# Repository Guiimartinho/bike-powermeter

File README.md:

<div align="center">

# Bike Power Meter

**Medidor de potência para bicicleta, aberto do extensômetro ao pod: torque por ponte de classe transdutor colada no braço do pedivela, cadência por acelerômetro, potência por BLE e ANT+. Par do [GNSS Bike Computer](https://github.com/Guiimartinho/gnss-bike-computer).**

</div>

Um módulo colado na face interna do braço esquerdo do pedivela. A ponte de extensômetros mede a **deformação do próprio braço**, que é o elemento elástico; o conversor lê a ponte em 24 bits, o acelerômetro dá o ângulo e a cadência, e o rádio publica potência, cadência e equilíbrio como qualquer medidor comercial — em **BLE Cycling Power** e **ANT+ Bicycle Power**, para o ciclocomputador do projeto ou para qualquer aplicativo.

O firmware é **obra original** em C puro sobre Zephyr, não um port. A placa, o pod e todos os desenhos são **gerados por programa** a partir dos documentos de [`hardware_powermeter/`](hardware_powermeter/README.md), pela mesma ideia do ciclocomputador: um gerador, um dry run, e nenhum número que não venha de uma ficha ou de uma medida.

> [!WARNING]
> **Nada foi fabricado, impresso, soldado nem colado, e o firmware nunca rodou.** Não existe placa física, nenhum extensômetro foi colado num pedivela, nenhum componente passou por bancada e nenhuma linha de código foi vista funcionando: tudo o que está escrito abaixo foi verificado no PC. As medidas do braço do pedivela são **lugares reservados** — ninguém mediu o braço. O estado de cada área está em [docs/07-status.md](docs/07-status.md).

## Índice

- [Visão geral](#visão-geral)
- [O aparelho](#o-aparelho)
- [Como a potência sai da deformação](#como-a-potência-sai-da-deformação)
- [Componentes](#componentes)
- [Funcionalidades](#funcionalidades)
- [Início rápido](#início-rápido)
- [Estrutura](#estrutura)
- [Documentação](#documentação)
- [Estado e próximos passos](#estado-e-próximos-passos)
- [Créditos e licença](#créditos-e-licença)

## Visão geral

```mermaid
flowchart LR
    subgraph POD["Pod colado no braço esquerdo"]
        G["Ponte S5229<br/>5 kΩ, uma peça"] -->|"2 mV"| A["ADS1220<br/>24 bits, ganho 128"]
        I["BMA400<br/>ângulo e cadência"] --> M["nRF54L15<br/>HOLYIOT-26001-A"]
        T["TMP117<br/>±0,1 °C"] --> M
        A --> M
        P["nPM1100 + célula LiPo"] --> M
        C["conector magnético<br/>carga, serial, SWD"] --> P
    end
    M -- "BLE Cycling Power" --> CC["ciclocomputador<br/>ou qualquer app"]
    M -- "ANT+ Bicycle Power" --> CC
```

## O aparelho

<div align="center">

*O pod no braço do pedivela. O braço é um lugar reservado, desenhado da classe (170 mm entre eixos) até o do dono ser medido; o pod, a placa e a ponte são a geometria real do projeto.*

</div>

### O produto, peça por peça

| | |
|---|---|
|  |  |
| *A pilha inteira: tampa, anel O, placa, célula e concha* | *De lado: 7,7 mm do fundo ao topo da tampa* |
|  |  |
| *Aberto: a ponte fica no **braço**, não no pod, e cinco fios sobem por um rasgo no fundo* | *A ponte S5229 colada na face interna do braço* |

### O pod

| | |
|---|---|
|  |  |
| *Fechado: 73,5 × 20,0 × 7,7 mm, 14,3 g estimados* | *Explodido: concha, célula, placa, anel O e tampa* |
|  |  |
| *Aberto, com a placa assentada* | *A célula no berço, no passo em que ela entra* |
|  |  |
| *A tampa por dentro: sulco do anel O, dedos da placa e o ressalto que comprime a junta da porta* | *Por baixo: a base de colagem de 14 mm, o relevo de 0,5, o rasgo dos fios, o bolso do extensômetro e a canaleta do feixe* |

### A placa

| | |
|---|---|
|  |  |
| *A placa, 50 × 16 mm em 4 camadas, 58 peças* | *O verso: pads de teste e o que não precisa ser alcançado, sobre o fundo rebaixado do pod* |
|  |  |
| *Em ângulo, com o corpo real de cada peça* | *O mapa de montagem, peça a peça* |

O envelope de referência veio de **fotogrametria** sobre as fotos de imprensa de um medidor da classe, porque nenhum fabricante publica as medidas: 37 a 39 mm de comprimento, 18 a 22 de largura e 9 a 13 de altura, com a escala aferida por dois caminhos independentes ([docs/01](docs/01-visao-geral.md)). É contra esse número que o pod é medido.

## Como a potência sai da deformação

O que quase todo texto sobre medidores esconde: **o sensor não mede força, mede o quanto o braço entorta.**

```mermaid
flowchart LR
    F["força no pedal<br/>~500 N"] --> D["o braço flexiona<br/>~571 µε na borda"]
    D --> V["a ponte desequilibra<br/>~2,28 mV"]
    V --> N["ADS1220, ganho 128<br/>24 bits ratiométrico"]
    N --> TQ["torque<br/>zero, inclinação, temperatura"]
    TQ --> PW["potência = torque × ω"]
    ANG["BMA400<br/>ângulo e ω"] --> PW
```

Duas coisas foram **medidas e corrigidas** aqui, e as duas mudam o aparelho:

- **o padrão de extensômetro especificado estava errado.** A lista pedia padrão de cisalhamento a 45°, que é padrão de torquímetro de eixo; o braço do pedivela é uma viga em balanço. Na mesma seção, a grade a 45° lê 52 µε e a grade axial na borda lê 459 µε: **8,9 vezes mais** ([docs/06](docs/06-medicao-e-calibracao.md));
- **o braço Shimano é oco.** Com parede de 3 mm o momento de inércia cai de 9.333 para 7.504 mm⁴ e a deformação sobe de 459 para **571 µε**, 24 % a mais.

A ponte é **uma peça só**, não quatro colagens: o padrão S5229 do databook de classe transdutor, `N2K-13-S5229A-50C/DG/E3`, 5 kΩ ±5 %, matriz de 4,0 × 3,7 mm, ponte de Poisson já balanceada de fábrica. O código `13` é a autocompensação para alumínio; **sem ele escrito no pedido o fabricante embarca o `06`, que é o de aço**.

## Componentes

| Bloco | Peça | Por quê |
|---|---|---|
| Ponte | Micro-Measurements `N2K-13-S5229A-50C/DG/E3` | ponte completa numa colagem só, 5 kΩ (0,6 mA em vez de 3,0), balanceada de fábrica, autocompensada para alumínio |
| Conversor | TI ADS1220 | 0,26 µV RMS com ganho 128, 585 µA medindo, referência **ratiométrica** (a excitação é a referência, então a tensão da célula sai da conta) |
| Cadência e ângulo | Bosch BMA400 | 850 nA a 25 Hz; driver próprio, porque o `bosch,bma4xx` da árvore usa o mapa do BMA422 |
| Temperatura | TI TMP117 | ±0,1 °C para o ajuste do zero e da inclinação |
| MCU e rádio | **HOLYIOT-26001-A** (nRF54L15), antena cerâmica | 10,0 × 12,5 mm contra 16,5 × 12,0 do ME54BS13: o módulo era **26 % da área da placa**, mais que as 37 peças pequenas somadas, e é a única alavanca de tamanho que move alguma coisa. Custa o USB, que este SoC não tem ([09](hardware_powermeter/09-modulo-de-radio.md)) |
| Carga e 3,0 V | Nordic nPM1100 | carregador e buck numa peça, 800 nA |
| Excitação | TI TPS22916 | desliga a ponte entre amostras; é ela que faz os 5 kΩ valerem a pena |
| Bateria | LiPo de bolsa classe **`401123`** (4,0 × 11 × 23 mm, ≥ 78 mAh, dois fios, proteção integrada) | a 0,68 mA — ponte de 5 kΩ com o conversor em duty-cycle — são **114 h**, contra as 50 h do requisito. A premissa anterior, de 2,5 mm de espessura, não existe: naquele volume a célula vale ~49 mAh. Nenhuma loja foi alcançada: o envelope é **requisito de compra** |
| Conector | magnético de 6 contatos, **desenhado aqui** | carga, serial e SWD num cabo só, sem tampa de borracha para perder. Contatos chatos de ouro no aparelho e molas no cabo, para o pod poder ser vedado ([06](hardware_powermeter/06-conectores-e-pontos-de-teste.md#j101--conector-magnético)) |

Lista completa, com a ficha e o código de compra de cada peça: [`hardware_powermeter/01-lista-de-componentes.md`](hardware_powermeter/01-lista-de-componentes.md).

## Funcionalidades

| Funcionalidade | Estado |
|---|---|
| Torque por ponte, com zero, inclinação e ajuste de temperatura | modelo escrito e testado no PC (18 casos, 50 de 50 linhas) |
| Ângulo e cadência pelos cruzamentos de zero do eixo tangencial | modelo escrito e testado (18 casos, 113 de 113 linhas) |
| Potência, equilíbrio e eficiência por volta | modelo escrito e testado (12 casos, 80 de 80 linhas) |
| Calibração: zero, inclinação por mínimos quadrados, massa conhecida | modelo escrito e testado (18 casos, 135 de 135 linhas) |
| BLE Cycling Power (Measurement, Feature, Control Point, Vector) | compila; os bytes vêm do modelo testado; nunca visto por um cliente |
| Serviço de configuração por BLE, com **escrita cifrada obrigatória** | compila; nunca emparelhado |
| ANT+ Bicycle Power (páginas 1, 16, 18, 80, 81) | compila com `ANT=1`; nenhum canal aberto de verdade |
| Atualização por BLE (mcumgr + MCUboot) e recuperação serial pela **UART** do conector magnético | compila; recusa pedalando ou com bateria fraca |
| Placa e pod gerados por programa, com dry run | placa colocada; pod fecha **16 de 16** regras, com vedação por anel O, parafusos, retenção e dreno |

## Início rápido

**Pré-requisitos** (Windows): nRF Connect SDK v3.3.0 em `C:\ncs` com o toolchain `936afb6332`, SEGGER J-Link e um nRF54LM20 DK. Para o ANT, o add-on `sdk-ant` em `C:\ncs\sdk-ant`, depois de aceitar o acordo ANT+. Para os testes de host, MinGW-w64 GCC, CMake e Ninja. Para o CAD, KiCad 8 em `D:\KiCAD`. Detalhes em [docs/03-ambiente-build.md](docs/03-ambiente-build.md).

```sh
# Git Bash, na raiz do repositório
bash tools/fw/fw.sh build            # compila para o nRF54LM20 DK (sysbuild + MCUboot)
BOARD=pmboard/nrf54l15/cpuapp BUILD_DIR=zephyr_app/build_custom bash tools/fw/fw.sh build
ANT=1 BUILD_DIR=zephyr_app/build_ant bash tools/fw/fw.sh build   # com a pilha ANT+
bash tools/fw/host_tests.sh          # 9 conjuntos, 134 casos
bash tools/fw/host_tests.sh coverage # e falha abaixo de 95 % em qualquer módulo
python tools/fw/board_check.py       # confere o devicetree contra o silício, docs/02 e o esquemático
python tools/docs/mermaid_check.py   # valida os diagramas da documentação
python tools/verificar_tudo.py       # a verificação inteira, três vezes
```

A cadeia de CAD, com o intérprete certo de cada etapa (o `fill_zones.py` **só** roda com o Python do KiCad), está em [`hardware_powermeter/cad/README.md`](hardware_powermeter/cad/README.md#a-cadeia).

O CI está **desligado**: a verificação é local.

## Estrutura

```mermaid
flowchart TB
    ROOT["bike_powermeter/"]
    ROOT --> ZA["zephyr_app/<br/>src (app · svc · model · rf) · include<br/>modules/pm_drivers (ADS1220, BMA400)<br/>boards · tests/host"]
    ROOT --> HW["hardware_powermeter/<br/>01 a 10 · cad (KiCad e geradores)<br/>esquematico · placa · pod (gerador, dry run, STL)<br/>datasheets (fora do git)"]
    ROOT --> DOCS["docs/<br/>01 a 07 · img/hardware (15 vistas)"]
    ROOT --> TOOLS["tools/<br/>fw · docs · verificar_tudo.py"]
    ROOT --> AI["CLAUDE.md · AGENTS.md · .claude/skills/"]
```

## Documentação

| Documento | Assunto |
|---|---|
| [01 · Visão geral](docs/01-visao-geral.md) | o que é, o envelope da classe por fotogrametria, as fases |
| [02 · Hardware](docs/02-hardware.md) | blocos da placa, pinos do módulo, orçamento de consumo, pod |
| [03 · Ambiente e build](docs/03-ambiente-build.md) | NCS v3.3.0, os três alvos, scripts, gravação |
| [04 · Arquitetura do firmware](docs/04-arquitetura-firmware.md) | os seis serviços, threads, pilhas, máquinas de estado |
| [05 · Protocolos](docs/05-protocolos.md) | BLE Cycling Power, ANT+ Bicycle Power, serviço de configuração com os UUID |
| [06 · Medição e calibração](docs/06-medicao-e-calibracao.md) | da deformação ao torque, flexão × cisalhamento, zero, inclinação, temperatura, saúde |
| [07 · Status](docs/07-status.md) | o que existe, o que foi verificado e como, o que falta |
| [Hardware](hardware_powermeter/README.md) | o esquemático, a placa, o pod, os dry runs e o que falta antes de fabricar |
| [CAD](hardware_powermeter/cad/README.md) | os geradores, as regras e as armadilhas medidas |
| [Pod](hardware_powermeter/pod/README.md) | o gerador do invólucro, as 32 regras do dry run e o que é decisão do desenho |
| [Módulo de rádio](hardware_powermeter/09-modulo-de-radio.md) | o HOLYIOT-26001-A: por que entrou, o que o nRF54L15 muda, pinagem, mecânica, a antena |
| [A classe medida](hardware_powermeter/12-comparacao-com-a-classe.md) | o 4iiii Precision 3+ e o U2e V4 contra o nosso, e o que custaria chegar ao alvo de envelope |
| [CHANGELOG](CHANGELOG.md) | histórico de mudanças |

## Estado e próximos passos

- **Feito em 2026-09-27:** a documentação de requisitos, arquitetura, protocolos e método de medição com as referências; a lista de componentes fechada por ficha; os nove módulos do modelo escritos e testados no PC (134 casos, 100 % das linhas, doze mutações mortas); o firmware embarcado inteiro compilando com **zero avisos** nos três alvos; o esquemático, a placa e o pod gerados por programa com os dois dry runs.
- **Feito em 2026-09-28:** a ponte fechada numa peça só (S5229 de 5 kΩ) com a designação de compra dos braços do dono; a correção do padrão de extensômetro (flexão, não cisalhamento: 8,9 vezes mais sinal); o roteador passou a ser julgado pelo **DRC do KiCad** em vez da própria contabilidade; três defeitos mecânicos do pod medidos e corrigidos, e o dry run fechou **12 de 12**.
- **Falta antes de fabricar:** fechar o roteamento, medir o pedivela do dono (quatro números), escolher a célula, fechar o conector magnético e conferir o empilhamento com o fabricante. A lista está em [`hardware_powermeter/README.md`](hardware_powermeter/README.md#antes-de-mandar-fabricar).
- **Depois:** bancada com massas de 5 a 20 kg contra o braço instrumentado, prova de estrada contra um medidor de referência até ±2 %, e a fase 2 no eixo de pedal.

## Créditos e licença

Projeto de Luiz Guilherme Ito. As referências técnicas — notas de aplicação dos fabricantes, databooks de extensometria, normas e artigos — estão citadas nos documentos que as usam, principalmente em [`docs/06-medicao-e-calibracao.md`](docs/06-medicao-e-calibracao.md) e [`hardware_powermeter/01-lista-de-componentes.md`](hardware_powermeter/01-lista-de-componentes.md).

Licença **CC BY-NC 4.0** ([`LICENSE`](LICENSE)), a mesma do GNSS Bike Computer: copiar, estudar, modificar e redistribuir com atribuição, **sem uso comercial**. Não é licença aprovada pela Open Source Initiative, que não admite restrição de uso, e foi escolhida por isso. O firmware deste projeto é obra original, não um port.

O material do ANT+ — perfis de dispositivo, código sob a ANT+ Shared Source License, chave de rede — **nunca entra neste repositório**: o ANT+ Adopter Agreement proíbe redistribuir. O que existe aqui é código próprio chamando a API do add-on. As fichas dos fabricantes ficam fora do git.

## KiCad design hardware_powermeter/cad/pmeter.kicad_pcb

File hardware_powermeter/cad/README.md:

# CAD da placa

Os geradores do KiCad 8: esquemático, placa, roteamento, verificações,
3D e desenhos. É a cadeia do ciclocomputador
(`hardware_gnssbike/cad/`), portada em 2026-09-27 com o nome de projeto
`pmeter`, as tabelas desta placa e três correções no roteador que esta
placa, mais densa e mais estreita, obrigou a fazer. Nada aqui é
desenhado à mão: cada arquivo `.kicad_*` sai de um script, e cada
script diz de que documento ou ficha tirou cada número.

**Nesta página:** [A cadeia](#a-cadeia) · [Os arquivos](#os-arquivos) · [O que mudou em relação ao ciclocomputador](#o-que-mudou-em-relação-ao-ciclocomputador) · [As regras do dry run](#as-regras-do-dry-run) · [Armadilhas](#armadilhas)

> [!WARNING]
> Nada foi fabricado nem montado. A placa existe como
> `pmeter.kicad_pcb`; o que foi medido está em
> [08](../08-dry-run-2026-09-27.md) e, depois da troca do modulo, em
> [10](../10-dry-run-2026-09-28.md).

## A cadeia

```mermaid
flowchart LR
    SCH["make_sch.py<br/>raiz + 4 folhas"] --> CSCH["check_sch.py<br/>ERC, netlist × nets.py,<br/>geometria"]
    CSCH --> PDF["kicad-cli sch export pdf<br/>esquematico/pmeter-esquematico.pdf"]
    DXF["make_dxf.py<br/>contorno e zonas"] --> CDXF["check_dxf.py"]
    CDXF --> PCB["make_pcb.py<br/>coloca as 58 peças"]
    PCB --> ROUTE["route.py<br/>labirinto A* em 3 camadas"]
    ROUTE --> FILL["fill_zones.py<br/>malhas, Python do KiCad"]
    FILL --> DRC1["kicad-cli pcb drc<br/>_drc_all.json"]
    DRC1 --> REP["reparar.py<br/>fecha o que o DRC diz aberto"]
    REP --> FILL2["fill_zones.py de novo"]
    FILL2 --> CPCB["check_pcb.py --como-esta<br/>DRC, contorno, redes"]
    CPCB --> DRY["dry_run_pcb.py<br/>24 regras das fichas"]
    DRY --> M3D["make_3d.py<br/>GLB e vistas placa-3d-*.png"]
    M3D --> M2D["make_2d.py · montagem.py<br/>placa/pmeter-pcb.pdf, pmeter-montagem.pdf"]
    M3D --> POD["pod/make_pod.py"]
```

Da raiz do repositório, com o Python do sistema salvo onde está dito:

```
python hardware_powermeter/cad/make_sch.py
python hardware_powermeter/cad/check_sch.py
"D:/KiCAD/bin/kicad-cli.exe" sch export pdf --output hardware_powermeter/esquematico/pmeter-esquematico.pdf hardware_powermeter/cad/pmeter.kicad_sch
python hardware_powermeter/cad/make_dxf.py
python hardware_powermeter/cad/check_dxf.py
python hardware_powermeter/cad/make_pcb.py
python hardware_powermeter/cad/route.py
"D:/KiCAD/bin/python.exe" hardware_powermeter/cad/fill_zones.py
cd hardware_powermeter/cad && "D:/KiCAD/bin/kicad-cli.exe" pcb drc --severity-all --format json -o _drc_all.json pmeter.kicad_pcb
python hardware_powermeter/cad/reparar.py
"D:/KiCAD/bin/python.exe" hardware_powermeter/cad/fill_zones.py
python hardware_powermeter/cad/check_pcb.py --como-esta
python hardware_powermeter/cad/dry_run_pcb.py
python hardware_powermeter/cad/make_3d.py
python hardware_powermeter/cad/make_2d.py
python hardware_powermeter/cad/montagem.py
python hardware_powermeter/pod/dry_run_pod.py
python hardware_powermeter/pod/make_pod.py
```

O tamanho da placa sai de `make_dxf.py` (`W`, `H`) e pode ser
experimentado sem editar o arquivo: `PMETER_W=48 python make_pcb.py`. O
colocador diz o que não coube e o roteador diz o que não ligou; foi assim
que o alvo de 48 × 16 de `docs/02` virou os **47 × 14** registrados em
[04](../04-placa.md#o-contorno).

## Os arquivos

| Arquivo | O que é |
|---|---|
| `parts.py` | as 58 peças com os pinos numerados pela ficha; `confirmed=False` marca as **duas** pinagens não lidas em ficha: o conector magnético genérico e o módulo de rádio, cujo mapa saiu do desenho mecânico do anúncio |
| `nets.py` | os 43 nós, pino a pino, e os pinos deixados abertos de propósito |
| `sheets.py`, `blocos.py`, `simbolos.py` | as 4 folhas, os blocos funcionais de cada uma e os símbolos da biblioteca do KiCad que têm a pinagem certa |
| `sch_lib.py`, `ksym.py`, `make_sch.py`, `check_sch.py`, `make_pro.py` | o gerador do esquemático, o leitor de símbolos do KiCad, o projeto `.kicad_pro` com as classes de rede |
| `make_dxf.py`, `check_dxf.py` | o contorno (`contorno.dxf`), o furo de fixação M1,6 e as zonas (`zonas.dxf`): a área livre da antena cerâmica, o bloco de energia a 20 mm do módulo, o conector magnético, o canto analógico, os furos da ponte, os sensores, o Tag-Connect, a sombra da célula e a da tampa |
| `footprints.py`, `fp_load.py` | qual footprint cada peça usa (biblioteca do KiCad ou gerado aqui com a cota da ficha), os corpos 3D em VRML, as alturas |
| `make_pcb.py` | o colocador: posições fixas (módulo, conector magnético, furos da ponte, conector da célula), âncoras por zona, desacoplamento encostado no pino, o resto por conectividade; os planos de terra e a área sem plano sob o nó de chaveamento |
| `route.py` | o roteador: vias de terra por pad, labirinto A* em `F.Cu`, `In2.Cu` e `B.Cu`, costura de terra na borda, poda de vias soltas. `PAR` está **vazio** desde 2026-09-28: não há mais par diferencial na placa |
| `route_neg.py` | o segundo estágio, de congestão negociada (PathFinder, McMurchie e Ebeling 1995), chamado quando o labirinto empaca; recebe como obstáculo o cobre que não vai rotear. Cada rodada refaz **só as redes que estão no caminho umas das outras**, e a cada `RIPAGEM_TOTAL` rodadas refaz a placa inteira do zero |
| `reparar.py` | fecha as ligações que o **DRC** ainda chama de abertas, na grade da placa pronta: parte sempre de um pad, mira o cobre inteiro da rede e recusa desenhar o que não encosta |
| `fill_zones.py` | preenche as malhas com o Python do KiCad (só ele sabe) |
| `check_pcb.py` | a placa como o KiCad a vê: DRC, peças presentes uma vez, redes dos pads, sobreposições, contorno, furos, cabe no envelope do pod, planos, serigrafia |
| `dry_run_pcb.py` | as regras das fichas e da IPC-2221 medidas na placa ([abaixo](#as-regras-do-dry-run)) |
| `make_3d.py`, `make_2d.py`, `montagem.py`, `orientacao.py` | o GLB e as vistas `placa-3d-*.png`, o PDF das camadas, o desenho de montagem, a conferência de para onde cada conector olha |
| `3d/` | os corpos VRML desenhados aqui; `3d/real/` (fora do git) para STEP de fabricante, quando houver |

## O que mudou em relação ao ciclocomputador

Tudo o que é desta placa está nas tabelas, não no código: zonas em
`make_dxf.py`, `ANCORAS`, `JUNTO`, `BORDA_FIXA`, `DECOPLA`, `ATRAS`,
`NAO_ENCOSTA` e `CHAVEIA` em `make_pcb.py`, `CORRENTE`, `CHAVEADOS`,
`ANALOGICO` e `TERMICOS` em `dry_run_pcb.py`. O que saiu: o receptor
GNSS, o display, o sensor de luz, o painel solar e as regras deles
(`RF5` a `RF8`, `RF10`, `AL4`, `OP1`). O que entrou: o canto analógico
(`AN1`, `AN2`), a face de trás plana (`ME2`), o envelope do pod (`ME1`).

Três coisas no roteador, todas **medidas** nesta placa em 2026-09-27
(`route.py` explica cada uma no lugar):

| O que | Antes | Agora |
|---|---|---|
| Ordem das ligações de uma rede | a ordem da lista de pinos: uma rede com um pino em cada ponta da placa e um pull-up no meio era buscada de uma ponta à outra primeiro, pelo meio apinhado, e falhava ali | **a mais perto primeiro**: a árvore cresce do pino mais próximo do que já está ligado |
| O pescoço dentro do campo de pads | um pescoço 0,025 mm mais largo que a trilha mínima, ou uma classe 0,07 mais estrita, pedia as células a 0,15 mm de cada lado livres, que num passo de 0,5 mm são a isolação do vizinho; **nenhum pino de potência do nPM1100, do ADS1220 ou do TVS conseguia sair do pad** (`veio=1`) | dentro do campo a busca olha só a célula; o pescoço tem a largura mínima em pad de até 0,3 mm (`estreitos − PASSO`); a classe USB fica nos 0,127 do fabricante (`make_pro.py`) |
| Até onde o pescoço dura | até `FOLGA` além da caixa dos pads: a primeira célula fora ainda estava dentro do anel do pad vizinho e a trilha larga não cabia ali (`veio=14`) | até `EXTRA_CAMPO` = `FOLGA` + meia trilha + um passo da grade |

E uma no colocador: os resistores de configuração e os pull-ups
(`NAO_ENCOSTA`) ficam perto do CI mas não encostam no pino, para deixar o
anel do nPM1100 para o desacoplamento e para as saídas dos pinos de
potência.

## As regras do dry run

`dry_run_pcb.py` mede a placa contra as fichas, e imprime o que mediu, o
que violou e o que não pôde medir. Uma regra que não acha o que medir
**falha dizendo isso**.

| Regra | O que mede | Fonte |
|---|---|---|
| RF1, RF3, RF4 | nada sobre a área da antena; 5 mm em volta dela sem peça alheia; a antena cerâmica dentro da zona livre **e encostando numa borda da placa** | guia de montagem do HOLYIOT-26001-A ([09](../09-modulo-de-radio.md#a-antena-manda-no-layout)) |
| RF9 | 20 mm do módulo a fonte chaveada ou indutor | 7.2, Interference Isolation Rule |
| US1 | as duas linhas da serial não atravessam o retângulo sem plano do nó de chaveamento do buck, em camada nenhuma | `make_pcb.sem_plano_no_chaveamento`; **não há mais par diferencial**: o nRF54L15 não tem USB e a 115200 baud não há impedância a controlar |
| AL1 | desacoplamento a 0,5 mm do pino do módulo, 2 mm nos outros CIs, 5 mm nos de reserva | 7.2; fichas do nPM1100, ADS1220, BMA400, TMP117, MAX17048 |
| AL5 | o filtro pi no pino de alimentação do módulo | 7.2 |
| AL2 | largura por corrente, 10 °C de subida | IPC-2221B, 6.2 |
| AN1 | o canto analógico a 4 mm do buck e a 5 mm do módulo | SBAS501D 9.4.1; os números são deste projeto |
| AN2 | o filtro das entradas e da referência junto dos pinos, e `REFP0` no nó da excitação | SBAS501D 9.1.2, figura 9-11; SBAA532A 3.1 |
| GN1, GN2 | pads de terra ligados, via por pad do módulo; costura na borda a cada 5 mm | 7.2; λ/10 a 2,44 GHz |
| AL6 | nenhuma via sob pad térmico | SBAS501D 11.1; nPM1100 PS 8.3 |
| ME1 | a placa no envelope alvo do pod (57,6 × 17,6 por dentro) | docs/02 |
| ME2 | as peças da frente sob o teto da tampa (2,7 mm), o conector que a atravessa exceto, e a face de trás plana | docs/02, Pod; `make_dxf.TETO_TAMPA` |
| ME3 | o corpo cotado na ficha cabe no footprint | `footprints.PACOTE` |
| ME4, ME5, ME6 | os corpos 3D contra as ilhas: só se medem com modelo de fabricante (nenhum ainda) ou GLB | o dono, no 3D do ciclocomputador |
| RT1 | zero itens desconectados no DRC completo (`--severity-all`) | kicad-cli |

Não medidas aqui: RF2 (o lado de RF para a borda: `orientacao.py`), AL3
(o laço de chaveamento: a bancada), e ME4 e ME5 enquanto não houver STEP
de fabricante em `3d/real/`.

## Armadilhas

As do ciclocomputador valem todas (`CLAUDE.md`, seção 6): o
`check_pcb.py` regera a placa sem `--como-esta`; o `fill_zones.py` só com
o Python do KiCad; o `kicad-cli` de `D:/KiCAD/bin`; um render de cima
sai girado 180°; o VRML da biblioteca do KiCad põe vírgula entre todos os
índices. As desta placa:

- **`PMETER_W` muda o contorno, e as zonas seguem** (`make_dxf.XE`,
  `XM`): o bloco de energia acaba 20 mm antes do módulo, o conector
  magnético e o canto analógico ficam no meio. Um número solto nas zonas
  quebra isso.
- **Os pontos de teste ficam atrás** (`ATRAS`): a face de trás tem de ser
  plana para a célula, e um pad é plano. Uma peça com corpo posta atrás
  falha `ME2` e `PD4`.
- **Os furos da ponte são passantes** (`PASSANTE`): ocupam as duas faces
  no colocador e todas as camadas no roteador.
- **Nenhum dos dois estágios do roteador sabe dizer se ligou** (medido em
  2026-09-28). O sequencial conta ligações que achou e o negociado conta
  caminhos que planejou; o negociado fechou dizendo "96 ligações, 0 células
  disputadas" com **onze pads sem cobre nenhum**, entre eles os três
  terminais do `USB_DM`. Pior: o critério de aceitação era `n_ok_n > n_ok`,
  ou seja, mais ligações — não menos pads abertos —, e ao aceitar o
  resultado do negociado o cobre sequencial das redes que ele **não** rodou
  ia para o lixo. Quem julga o roteamento é o DRC do KiCad, e é por isso
  que o `reparar.py` existe e entra na cadeia entre dois DRC.
- **Cobre herdado tem de ser obstáculo para quem herda.** Passar ao
  negociado as trilhas que ele não vai rotear (`pre_seg`, `pre_via`) levou
  o DRC de 182 violações para 25: sem isso ele planeja sobre placa vazia e
  o cobre herdado cai em cima das trilhas dele.
- **Uma via não é de graça.** Ela atravessa todas as camadas, então tem de
  se afastar de todas as redes em todas elas. Uma via posta sem essa
  conferência custou dois curtos, um isolamento de furo e uma ponte de
  máscara — quatro erros por uma ligação que nem fechou
  (`route.via_cabe_aqui`).
- **`SO_FRENTE` é preferência, não lei.** O par USB foi calculado como
  microstrip de 90 Ω em `F.Cu`, e com isso como lei o `USB_DM` não fecha
  (16,7 mm por uma face cheia). O aparelho fala **full speed**, 12 Mbit/s:
  a busca tenta a frente nas duas folgas e só troca de camada se não
  houver caminho — e avisa quando trocou.
- **Rotear depois do `fill_zones.py` custa 4 ligações e 45 trilhas**
  (medido em 2026-09-28, mesma colocação e mesmo código). Direto do
  `make_pcb.py`: 70 ligações na primeira passagem, 36 falhas, 440 segmentos,
  31 não roteados. Depois do preenchimento: 64, 42, 395, 35. **Esvaziar as
  malhas não devolve o resultado bom** — testado —, então não é o cobre
  despejado: é o arquivo inteiro, que o pcbnew reescreve à sua maneira. O
  `route.py` recusa rodar sobre placa preenchida e diz o que rodar antes.
  E o roteador **é determinístico**: duas execuções da mesma entrada dão o
  mesmo arquivo, o que foi medido para descartar a outra hipótese.
- **O passe de encosto final também tem de medir.** Ele liga uma trilha que
  parou a um passo do próprio pad, e desenhava sem conferir nada: um pad
  aberto por 0,15 mm virava um curto de 1,4 mm de trilha. O roteador via os
  cinco pares perto demais, dizia, e gravava a placa. Hoje cada toco é
  medido antes de ser aceito e o que não passa deixa o pad aberto dizendo
  por quê.
- **O que NAO fecha as ligacoes que faltam** (tudo medido em 2026-09-29,
  sobre a placa com o modulo ligado; a linha de base e 30 itens
  desconectados com 0 erros de DRC e 16 regras cumpridas):

  | Tentativa | Resultado |
  |---|---|
  | Placa de 50 ou 52 mm | 33 desconectados. **Nao e falta de area**: a ocupacao e 23 % das tres camadas |
  | Trilha de sinal a 0,127 mm (o minimo declarado) | **identico**. O passo da grade e 0,15 mm, entao 0,023 mm nao muda uma celula |
  | Grade de 0,10 mm | 32, com 2 erros, e 8,5 min de roteamento |
  | Anel livre de 0,9 mm em volta dos CIs de passo fino | **nenhuma peca se moveu**: elas ja guardavam essa distancia |
  | Anel de 1,6 mm nos quatro CIs + folga de mascara 0,20 | 28, mas duas regras a menos (o desacoplamento afasta) |
  | Folga de mascara 0,20 / 0,14 | 29 / 28, a segunda com 3 erros de isolamento |
  | Celula movida para a direita + passivos de energia no verso | 32 |
  | Cinco ordens de roteamento diferentes | 11 a 43: **so troca quais redes falham** |

- **O fanout e o caminho, e ainda nao esta pronto.** Tirar cada ilha de
  passo fino para uma via ANTES de rotear - com a placa vazia - levou as
  redes que falham de **23 para 12** e as ligacoes roteadas de 81 para 85.
  Mas o numero do DRC piorou (30 para 42), porque o cobre do fanout que o
  roteamento nao usa vira fragmento e conta como item desconectado, e podar
  so o que sobra ainda nao ficou certo. E o passe **existe** em `pre_ligados`:
  o laco principal ja sabe partir de cobre pre-desenhado. E por aqui que a
  proxima rodada comeca.
- **O conector magnético é genérico**: `confirmed=False` em `parts.py`,
  e a janela da tampa segue o contorno dele; trocar a peça é trocar o
  footprint, a altura e rodar os dois dry runs.
- **Rip-up parcial sozinho DIVERGE nesta placa** (medido em 2026-09-28). O
  PathFinder refaz só as redes que estão no caminho umas das outras, e numa
  placa grande isso é quase todo mundo; aqui o teste de partilha é
  geométrico e acha poucas redes, então o conjunto fica pequeno e a pressão
  bate numa parede: as culpadas não têm para onde ir porque as inocentes
  estão congeladas, e o custo histórico não empurra quem nunca é refeito.
  As células disputadas subiram rodada após rodada — 420, 488, 528, 611,
  972, 1292, **1588 na rodada 10**, com duas ligações perdendo o caminho. A
  saída é a que a literatura usa quando o rip-up é parcial: uma **ripagem
  total a cada `RIPAGEM_TOTAL` rodadas** (hoje 6). As rodadas baratas
  refinam, a rodada cheia redistribui — e de quebra lava qualquer marca
  velha que um rip-up incremental tenha deixado em `uso`, que é o modo de
  falhar de um `_desmarcar` que não seja o inverso exato do `_marcar`. Com
  ela, as rodadas cheias caíram para 234, 199, 155 e 120.
- **As redes culpadas têm de ser anotadas onde o conflito é achado.** A
  célula que entra em `disputadas` é a do **caminho**, e o conflito está numa
  célula do disco de folga dele: procurar depois quem está nela em `uso`
  devolve a própria rede e quase nunca a outra, então a outra nunca era
  refeita e a rodada seguinte achava o mesmo conflito para sempre.

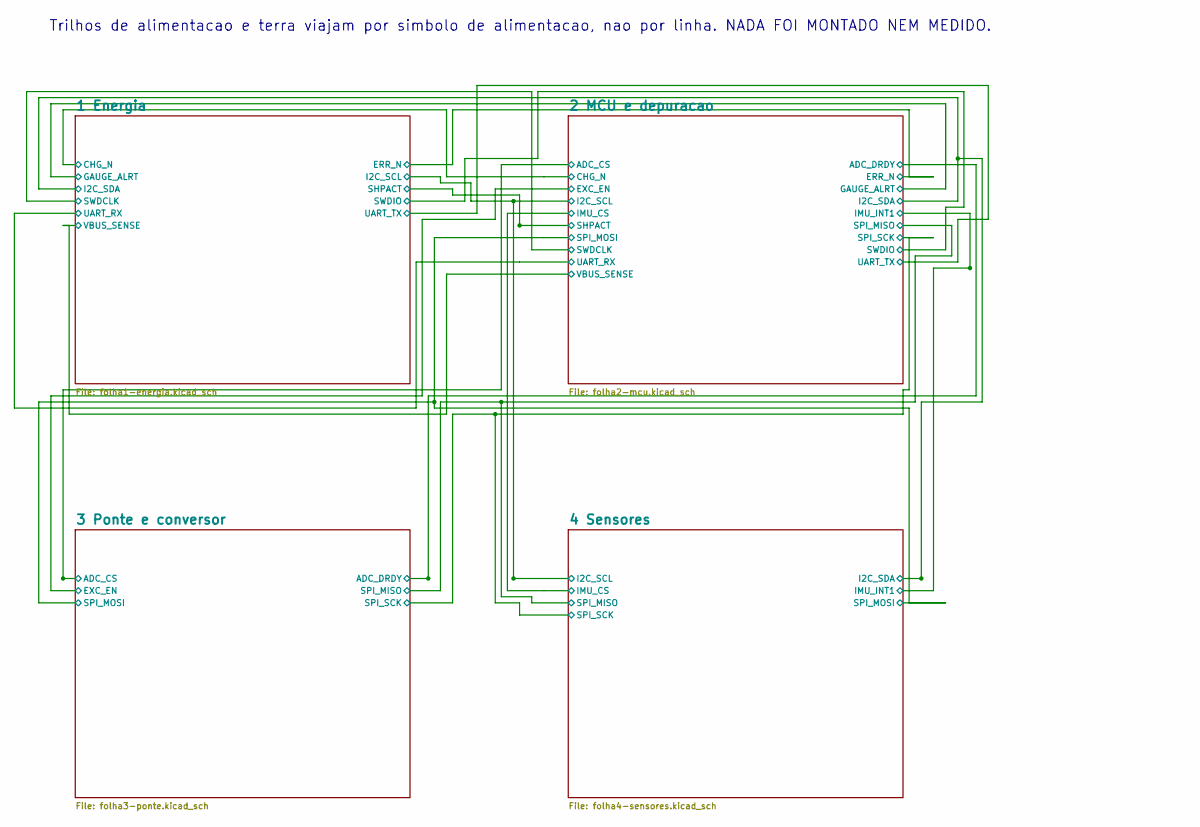
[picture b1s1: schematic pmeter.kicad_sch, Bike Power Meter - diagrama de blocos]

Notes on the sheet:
Trilhos de alimentacao e terra viajam por simbolo de alimentacao, nao por linha. NADA FOI MONTADO NEM MEDIDO.

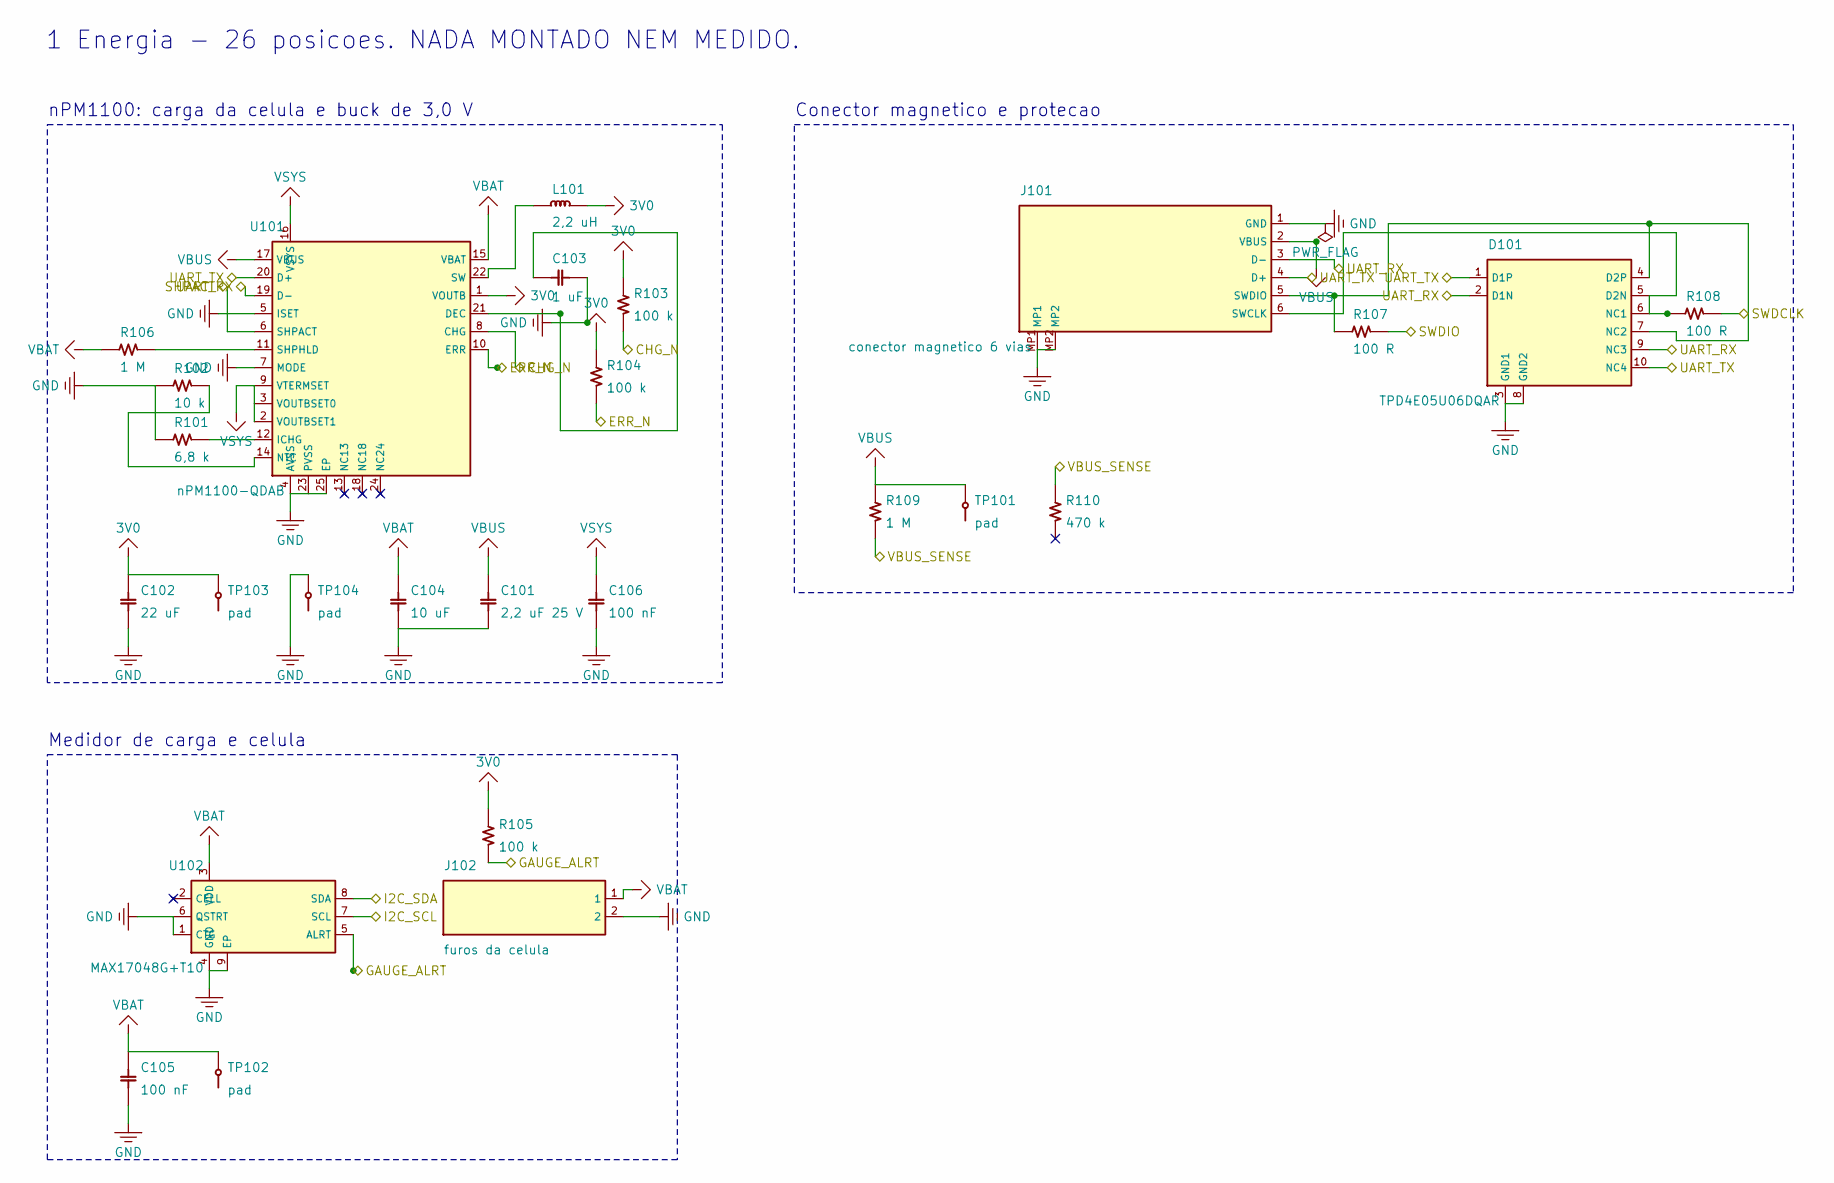
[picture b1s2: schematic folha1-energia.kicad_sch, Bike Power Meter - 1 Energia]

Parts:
C101: 2,2 uF 25 V; C_0603_1608Metric
C102: 22 uF; C_0603_1608Metric
C103: 1 uF; C_0402_1005Metric
C104: 10 uF; C_0603_1608Metric
C105, C106: 100 nF; C_0402_1005Metric
D101: TPD4E05U06DQAR; TPD4E05U06_USON-10_1x2.5mm_P0.5mm
J101: conector magnetico 6 vias; Pogo_Magnetico_6P_2x3_P2.5mm
J102: furos da celula; JST_SH_SM02B-SRSS-TB_1x02-1MP_P1.00mm_Horizontal
L101: 2,2 uH; L_0805_2012Metric
R101: 6,8 k; R_0402_1005Metric
R102: 10 k; R_0402_1005Metric
R103, R104, R105: 100 k; R_0402_1005Metric
R106, R109: 1 M; R_0402_1005Metric
R107, R108: 100 R; R_0402_1005Metric
R110: 470 k; R_0402_1005Metric
TP101, TP102, TP103, TP104: pad; TestPoint_Pad_D1.0mm
U101: nPM1100-QDAB; QFN-24-1EP_4x4mm_P0.5mm_EP2.7x2.7mm
U102: MAX17048G+T10; TDFN-8-1EP_2x2mm_P0.5mm_EP0.8x1.2mm

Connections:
3V0: C102.1, L101.2, R103.1, R104.1, R105.1, TP103.1, U101.1 (VOUTB); also elsewhere on the board
BUCK_SW: L101.1, U101.22 (SW)
CHG_N: R103.2, U101.8 (CHG); also elsewhere on the board
DEC: C103.1, U101.21 (DEC)
ERR_N: R104.2, U101.10 (ERR); also elsewhere on the board
GAUGE_ALRT: R105.2, U102.5 (ALRT); also elsewhere on the board
GND: C101.2, C102.2, C103.2, C104.2, C105.2, C106.2, D101.3 (GND1), D101.8 (GND2), J101.1 (GND), J101.MP1, J101.MP2, J102.2, R101.2, R102.2, TP104.1, U101.4 (AVSS), U101.5 (ISET), U101.7 (MODE), U101.23 (PVSS), U101.25 (EP), U102.1 (CTG), U102.4 (GND), U102.6 (QSTRT), U102.9 (EP); also elsewhere on the board
I2C_SCL: U102.7 (SCL); also elsewhere on the board
I2C_SDA: U102.8 (SDA); also elsewhere on the board
ICHG: R101.1, U101.12 (ICHG)
NTC: R102.1, U101.14 (NTC)
SHPACT: U101.6 (SHPACT); also elsewhere on the board
SHPHLD: R106.2, U101.11 (SHPHLD)
SWCLK_J: D101.5 (D2N), D101.6 (NC1), J101.6 (SWCLK), R108.1
SWDCLK: R108.2; also elsewhere on the board
SWDIO: R107.2; also elsewhere on the board
SWDIO_J: D101.4 (D2P), D101.7 (NC2), J101.5 (SWDIO), R107.1
UART_RX: D101.2 (D1N), D101.9 (NC3), J101.3 (D-), U101.19 (D-); also elsewhere on the board
UART_TX: D101.1 (D1P), D101.10 (NC4), J101.4 (D+), U101.20 (D+); also elsewhere on the board
VBAT: C104.1, C105.1, J102.1, R106.1, TP102.1, U101.15 (VBAT), U102.3 (VDD)
VBUS: C101.1, J101.2 (VBUS), R109.1, TP101.1, U101.17 (VBUS)
VBUS_SENSE: R109.2, R110.1; also elsewhere on the board
VSYS: C106.1, U101.2 (VOUTBSET1), U101.3 (VOUTBSET0), U101.9 (VTERMSET), U101.16 (VSYS); also elsewhere on the board

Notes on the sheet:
Conector magnetico e protecao
nPM1100: carga da celula e buck de 3,0 V
Medidor de carga e celula
1 Energia - 26 posicoes. NADA MONTADO NEM MEDIDO.

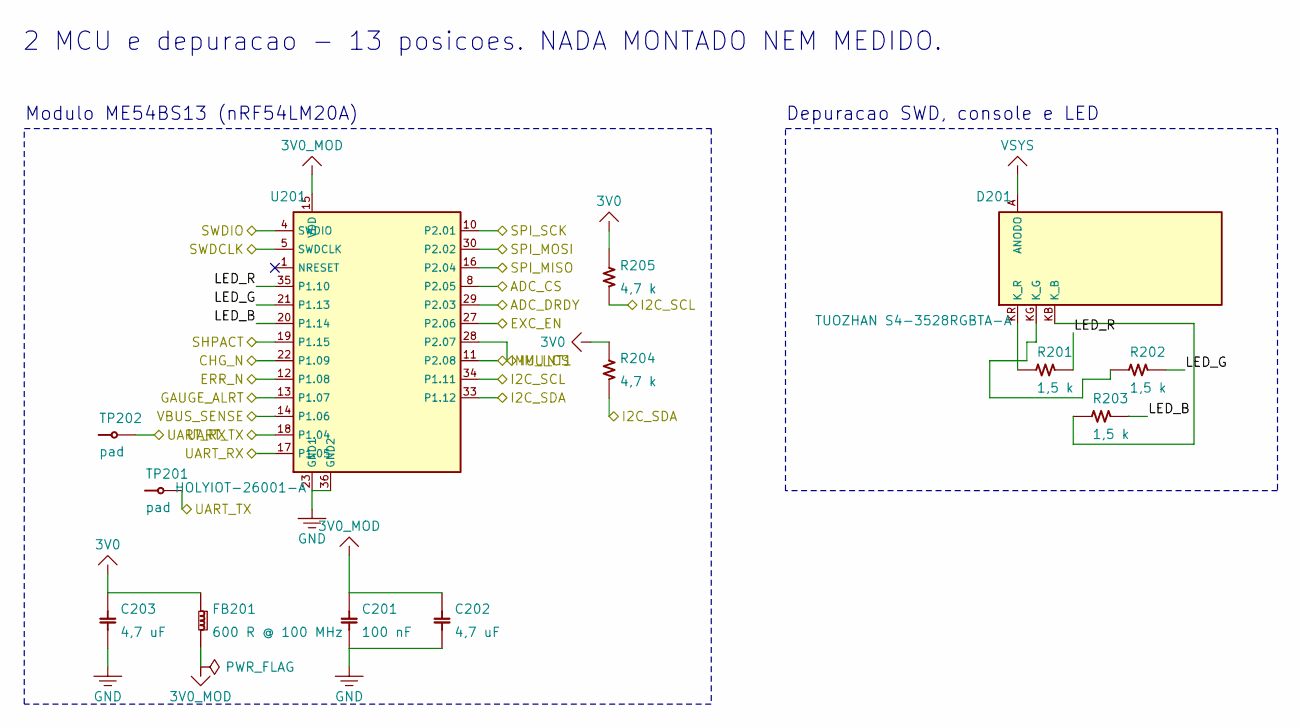
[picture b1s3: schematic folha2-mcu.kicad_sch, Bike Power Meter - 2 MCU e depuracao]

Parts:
C201: 100 nF; C_0402_1005Metric
C202, C203: 4,7 uF; C_0603_1608Metric
D201: TUOZHAN S4-3528RGBTA-A; LED_RGB_3528_3.5x2.8mm
FB201: 600 R @ 100 MHz; L_0603_1608Metric
R201, R202, R203: 1,5 k; R_0402_1005Metric
R204, R205: 4,7 k; R_0402_1005Metric
TP201, TP202: pad; TestPoint_Pad_D1.0mm
U201: HOLYIOT-26001-A; HOLYIOT_26001A_10x12.5mm

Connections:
3V0: C203.1, FB201.1, R204.1, R205.1; also elsewhere on the board
3V0_MOD: C201.1, C202.1, FB201.2, U201.15 (VDD)
ADC_CS: U201.8 (P2.05); also elsewhere on the board
ADC_DRDY: U201.29 (P2.03); also elsewhere on the board
CHG_N: U201.22 (P1.09); also elsewhere on the board
ERR_N: U201.12 (P1.08); also elsewhere on the board
EXC_EN: U201.27 (P2.06); also elsewhere on the board
GAUGE_ALRT: U201.13 (P1.07); also elsewhere on the board
GND: C201.2, C202.2, C203.2, U201.23 (GND), U201.36 (GND); also elsewhere on the board
I2C_SCL: R205.2, U201.34 (P1.11); also elsewhere on the board
I2C_SDA: R204.2, U201.33 (P1.12); also elsewhere on the board
IMU_CS: U201.28 (P2.07); also elsewhere on the board
IMU_INT1: U201.11 (P2.08); also elsewhere on the board
LED_B: R203.2, U201.20 (P1.14)
LED_G: R202.2, U201.21 (P1.13)
LED_KB: D201.KB (K_B), R203.1
LED_KG: D201.KG (K_G), R202.1
LED_KR: D201.KR (K_R), R201.1
LED_R: R201.2, U201.35 (P1.10)
SHPACT: U201.19 (P1.15); also elsewhere on the board
SPI_MISO: U201.16 (P2.04); also elsewhere on the board
SPI_MOSI: U201.30 (P2.02); also elsewhere on the board
SPI_SCK: U201.10 (P2.01); also elsewhere on the board
SWDCLK: U201.5 (SWDCLK); also elsewhere on the board
SWDIO: U201.4 (SWDIO); also elsewhere on the board
UART_RX: TP202.1, U201.17 (P1.05); also elsewhere on the board
UART_TX: TP201.1, U201.18 (P1.04); also elsewhere on the board
VBUS_SENSE: U201.14 (P1.06); also elsewhere on the board
VSYS: D201.A (ANODO); also elsewhere on the board

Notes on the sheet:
Modulo ME54BS13 (nRF54LM20A)
Depuracao SWD, console e LED
2 MCU e depuracao - 13 posicoes. NADA MONTADO NEM MEDIDO.

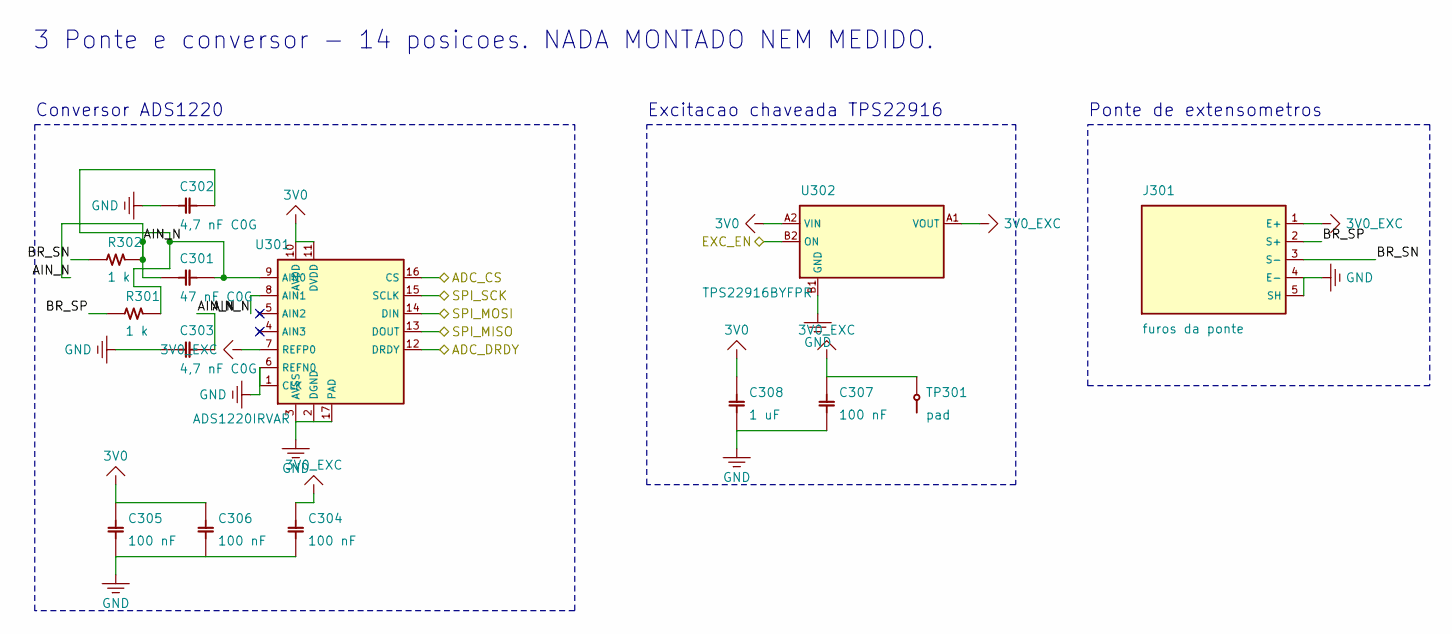
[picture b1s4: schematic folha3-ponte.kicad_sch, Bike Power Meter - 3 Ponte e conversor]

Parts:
C301: 47 nF C0G; C_0402_1005Metric
C302, C303: 4,7 nF C0G; C_0402_1005Metric
C304, C305, C306, C307: 100 nF; C_0402_1005Metric
C308: 1 uF; C_0402_1005Metric
J301: furos da ponte; Furos_Ponte_5x1.5mm_P2mm
R301, R302: 1 k; R_0402_1005Metric
TP301: pad; TestPoint_Pad_D1.0mm
U301: ADS1220IRVAR; Texas_RVA_VQFN-16-1EP_3.5x3.5mm_P0.5mm_EP2.14x2.14mm
U302: TPS22916BYFPR; TPS22916_DSBGA-4_0.78x0.78mm_P0.4mm

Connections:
3V0: C305.1, C306.1, C308.1, U301.10 (AVDD), U301.11 (DVDD), U302.A2 (VIN); also elsewhere on the board
3V0_EXC: C304.1, C307.1, J301.1 (E+), TP301.1, U301.7 (REFP0), U302.A1 (VOUT)
ADC_CS: U301.16 (CS); also elsewhere on the board
ADC_DRDY: U301.12 (DRDY); also elsewhere on the board
AIN_N: C301.2, C303.1, R302.2, U301.8 (AIN1)
AIN_P: C301.1, C302.1, R301.2, U301.9 (AIN0)
BR_SN: J301.3 (S-), R302.1
BR_SP: J301.2 (S+), R301.1
EXC_EN: U302.B2 (ON); also elsewhere on the board
GND: C302.2, C303.2, C304.2, C305.2, C306.2, C307.2, C308.2, J301.4 (E-), J301.5 (SH), U301.1 (CLK), U301.2 (DGND), U301.3 (AVSS), U301.6 (REFN0), U301.17 (PAD), U302.B1 (GND); also elsewhere on the board
SPI_MISO: U301.13 (DOUT); also elsewhere on the board
SPI_MOSI: U301.14 (DIN); also elsewhere on the board
SPI_SCK: U301.15 (SCLK); also elsewhere on the board

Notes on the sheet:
Ponte de extensometros
Excitacao chaveada TPS22916
Conversor ADS1220
3 Ponte e conversor - 14 posicoes. NADA MONTADO NEM MEDIDO.

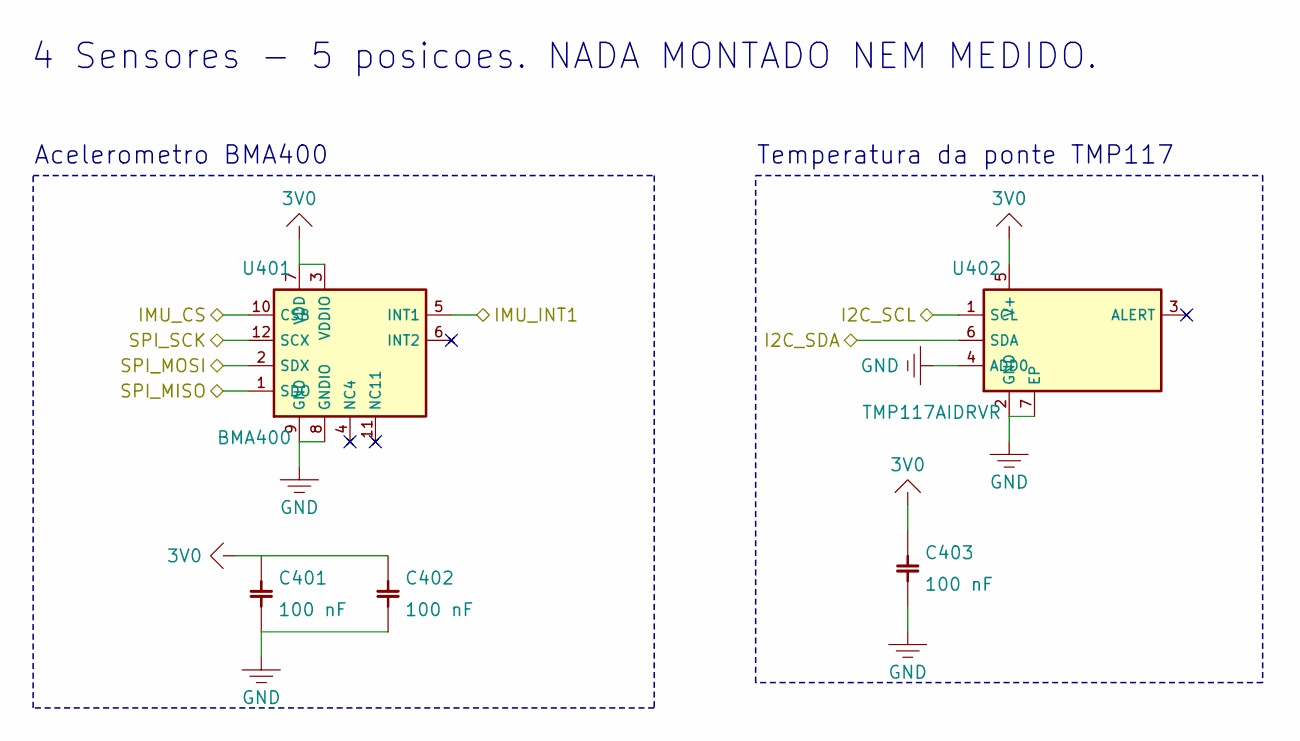
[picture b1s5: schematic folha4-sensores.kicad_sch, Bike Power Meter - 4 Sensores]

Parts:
C401, C402, C403: 100 nF; C_0402_1005Metric
U401: BMA400; LGA-12_2x2mm_P0.5mm
U402: TMP117AIDRVR; WSON-6-1EP_2x2mm_P0.65mm_EP1x1.6mm

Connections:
3V0: C401.1, C402.1, C403.1, U401.3 (VDDIO), U401.7 (VDD), U402.5 (V+); also elsewhere on the board
GND: C401.2, C402.2, C403.2, U401.8 (GNDIO), U401.9 (GND), U402.2 (GND), U402.4 (ADD0), U402.7 (EP); also elsewhere on the board
I2C_SCL: U402.1 (SCL); also elsewhere on the board
I2C_SDA: U402.6 (SDA); also elsewhere on the board
IMU_CS: U401.10 (CSB); also elsewhere on the board
IMU_INT1: U401.5 (INT1); also elsewhere on the board
SPI_MISO: U401.1 (SDO); also elsewhere on the board
SPI_MOSI: U401.2 (SDX); also elsewhere on the board
SPI_SCK: U401.12 (SCX); also elsewhere on the board

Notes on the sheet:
Acelerometro BMA400
Temperatura da ponte TMP117
4 Sensores - 5 posicoes. NADA MONTADO NEM MEDIDO.

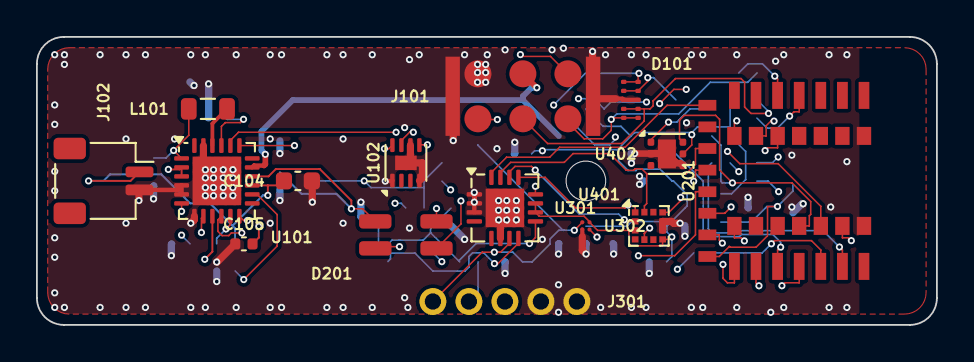
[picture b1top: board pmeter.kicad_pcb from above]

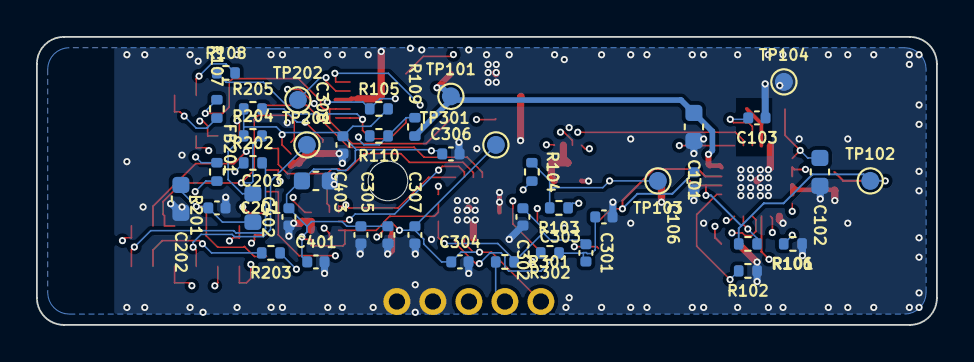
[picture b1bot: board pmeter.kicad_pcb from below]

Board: 4 copper layers, 50.0 x 16.0 mm, 58 parts (43 on the bottom side), 43 nets.

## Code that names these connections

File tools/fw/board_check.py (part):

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        if len(cells) < 2:
            continue
        # uma linha pode trazer vários sinais e vários pinos, na mesma ordem
        # (`LED_R`, `LED_G`, `LED_B` | P1.06, P1.08, P1.09): cada pino leva o
        # seu, não a célula inteira.
        signals = [s.strip().strip("`") for s in cells[0].split(",")]
        found = re.findall(r"P(\d)\.(\d\d)", cells[1])
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
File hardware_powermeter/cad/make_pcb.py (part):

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    "C401": "U401", "C402": "U401", "C403": "U402",
}
# Two terminal parts that sit NEAR their chip but do not hug a pin: a
# resistor to a static pin (ICHG, NTC, SHPHLD) or a pull-up has no loop to
# keep short, and on the ring round the nPM1100 they took the room the
# decoupling and the escapes of the power pins needed (the router died
# 0,2 mm out of VSYS, VBUS and VBAT on 2026-09-27). They are placed from
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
